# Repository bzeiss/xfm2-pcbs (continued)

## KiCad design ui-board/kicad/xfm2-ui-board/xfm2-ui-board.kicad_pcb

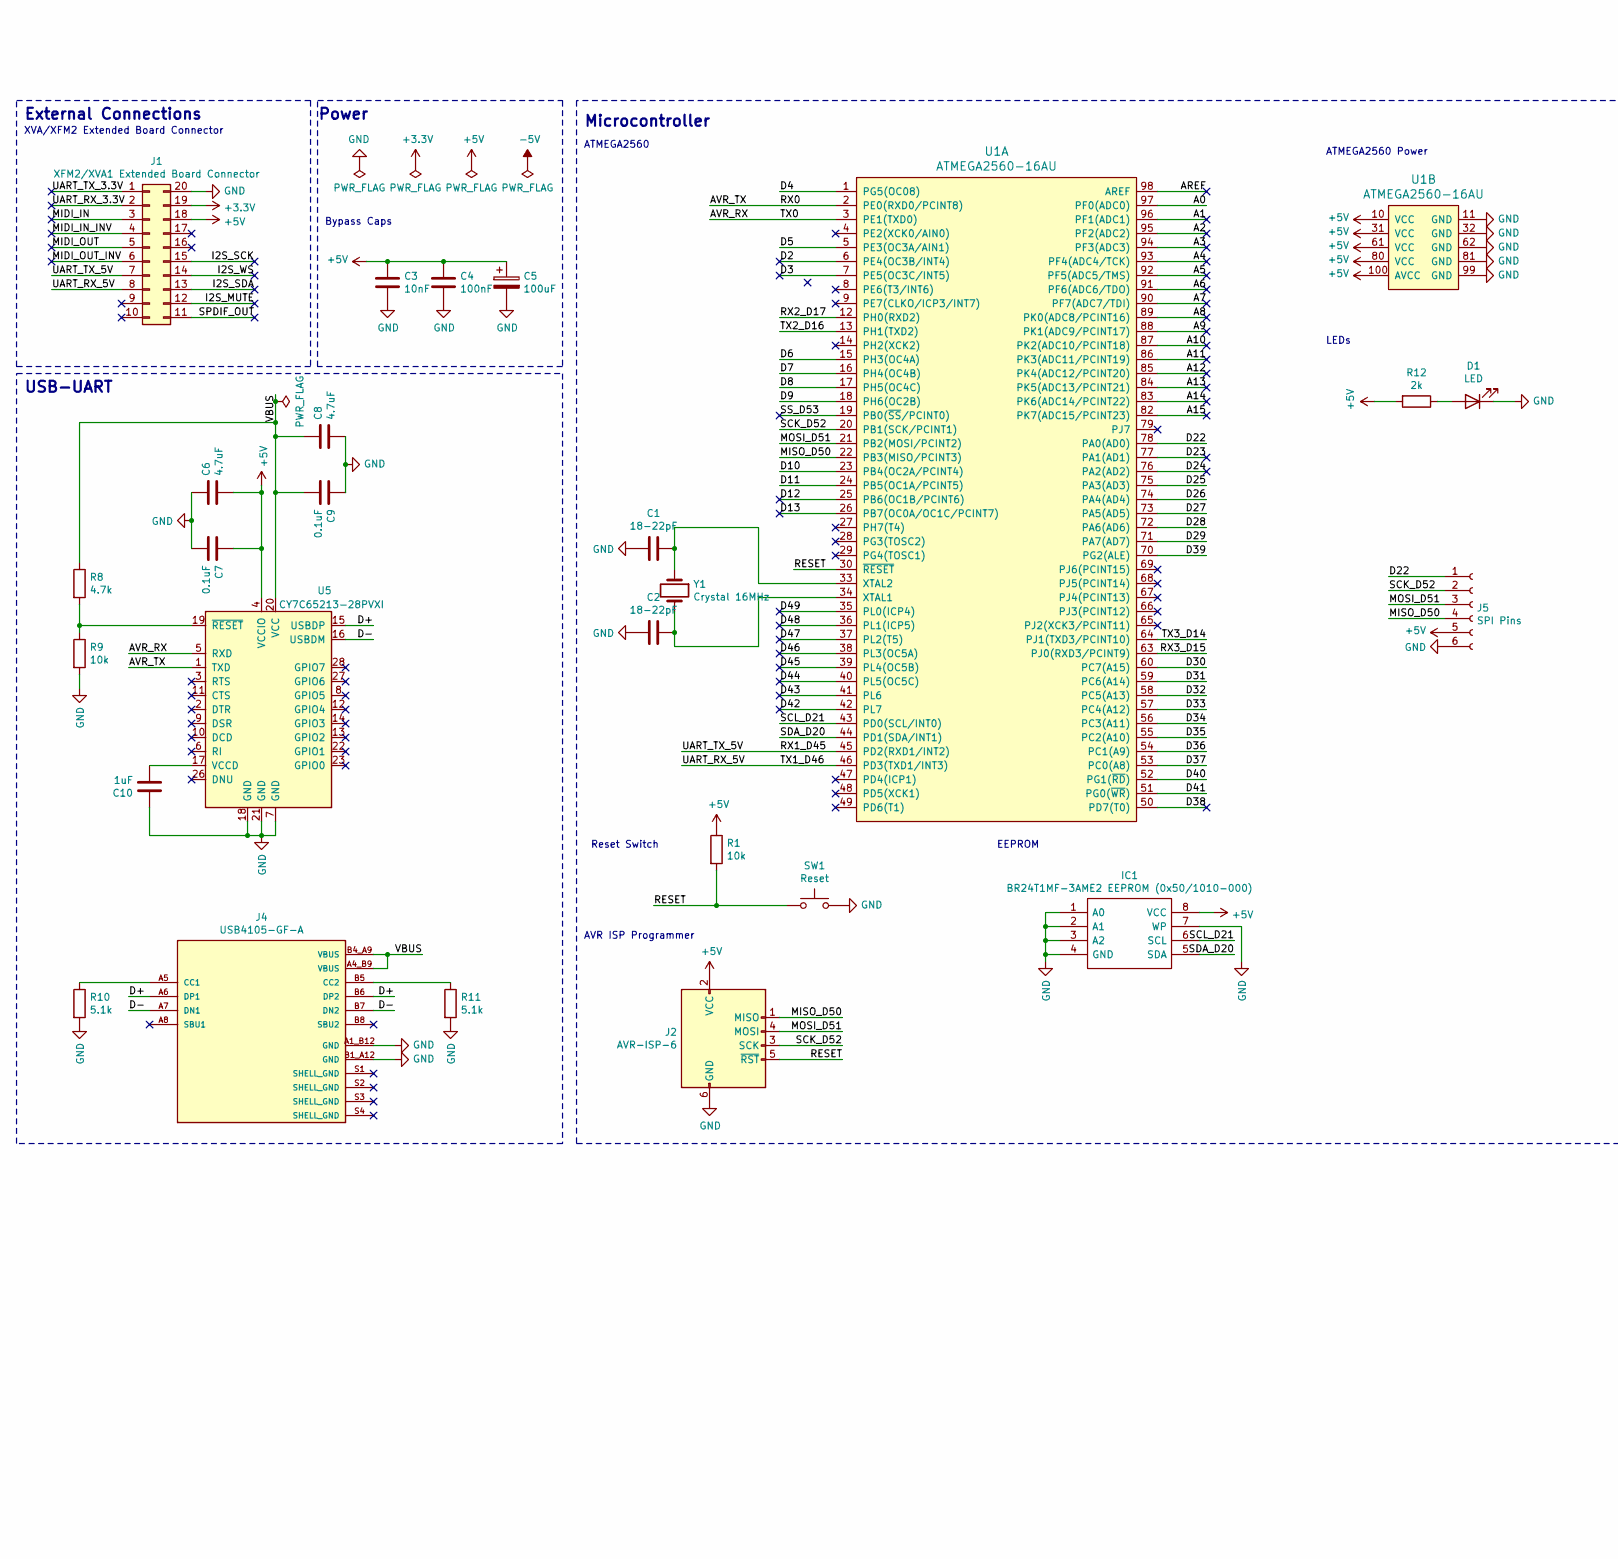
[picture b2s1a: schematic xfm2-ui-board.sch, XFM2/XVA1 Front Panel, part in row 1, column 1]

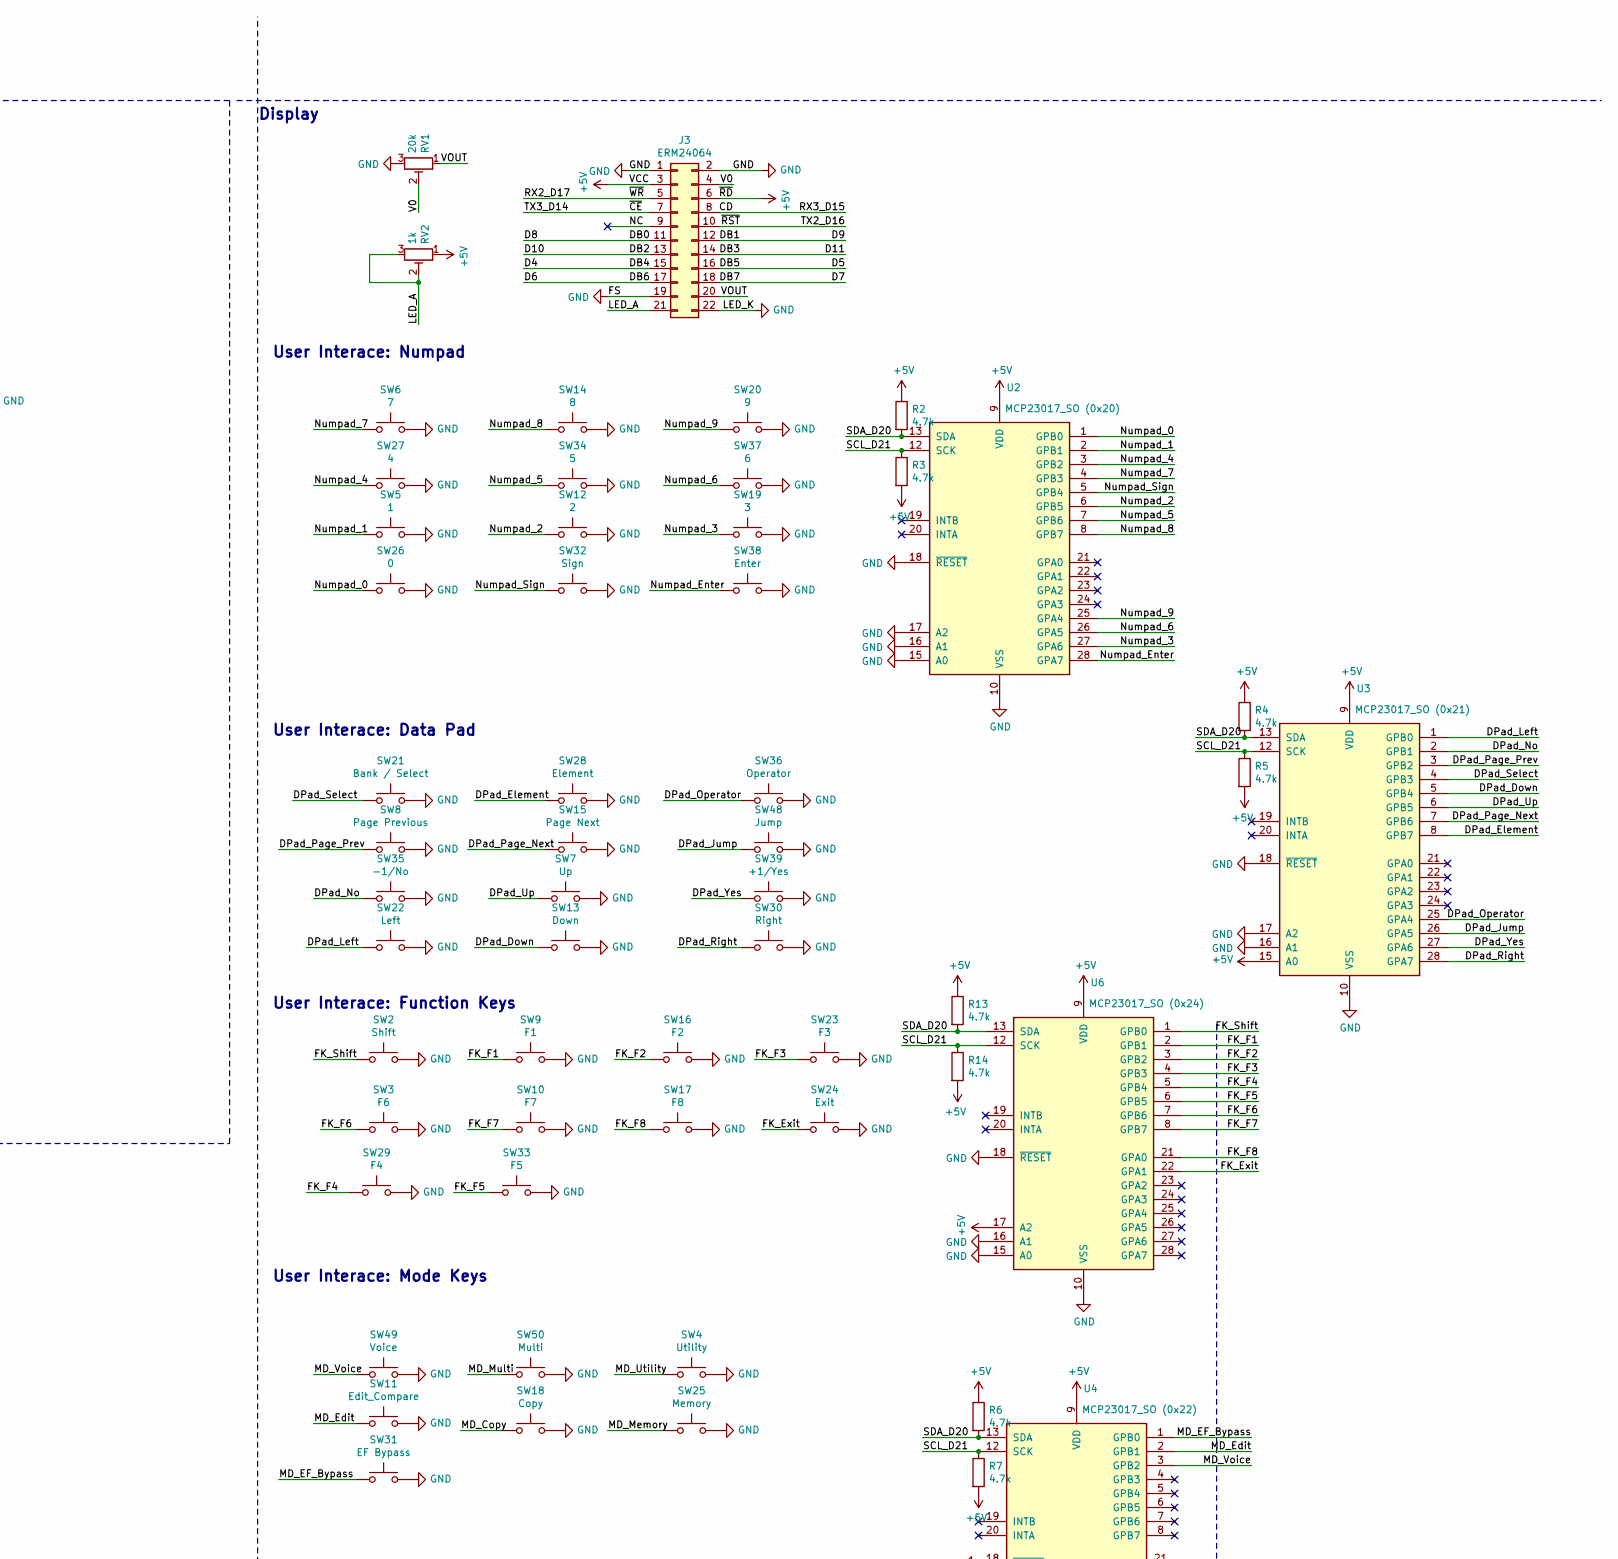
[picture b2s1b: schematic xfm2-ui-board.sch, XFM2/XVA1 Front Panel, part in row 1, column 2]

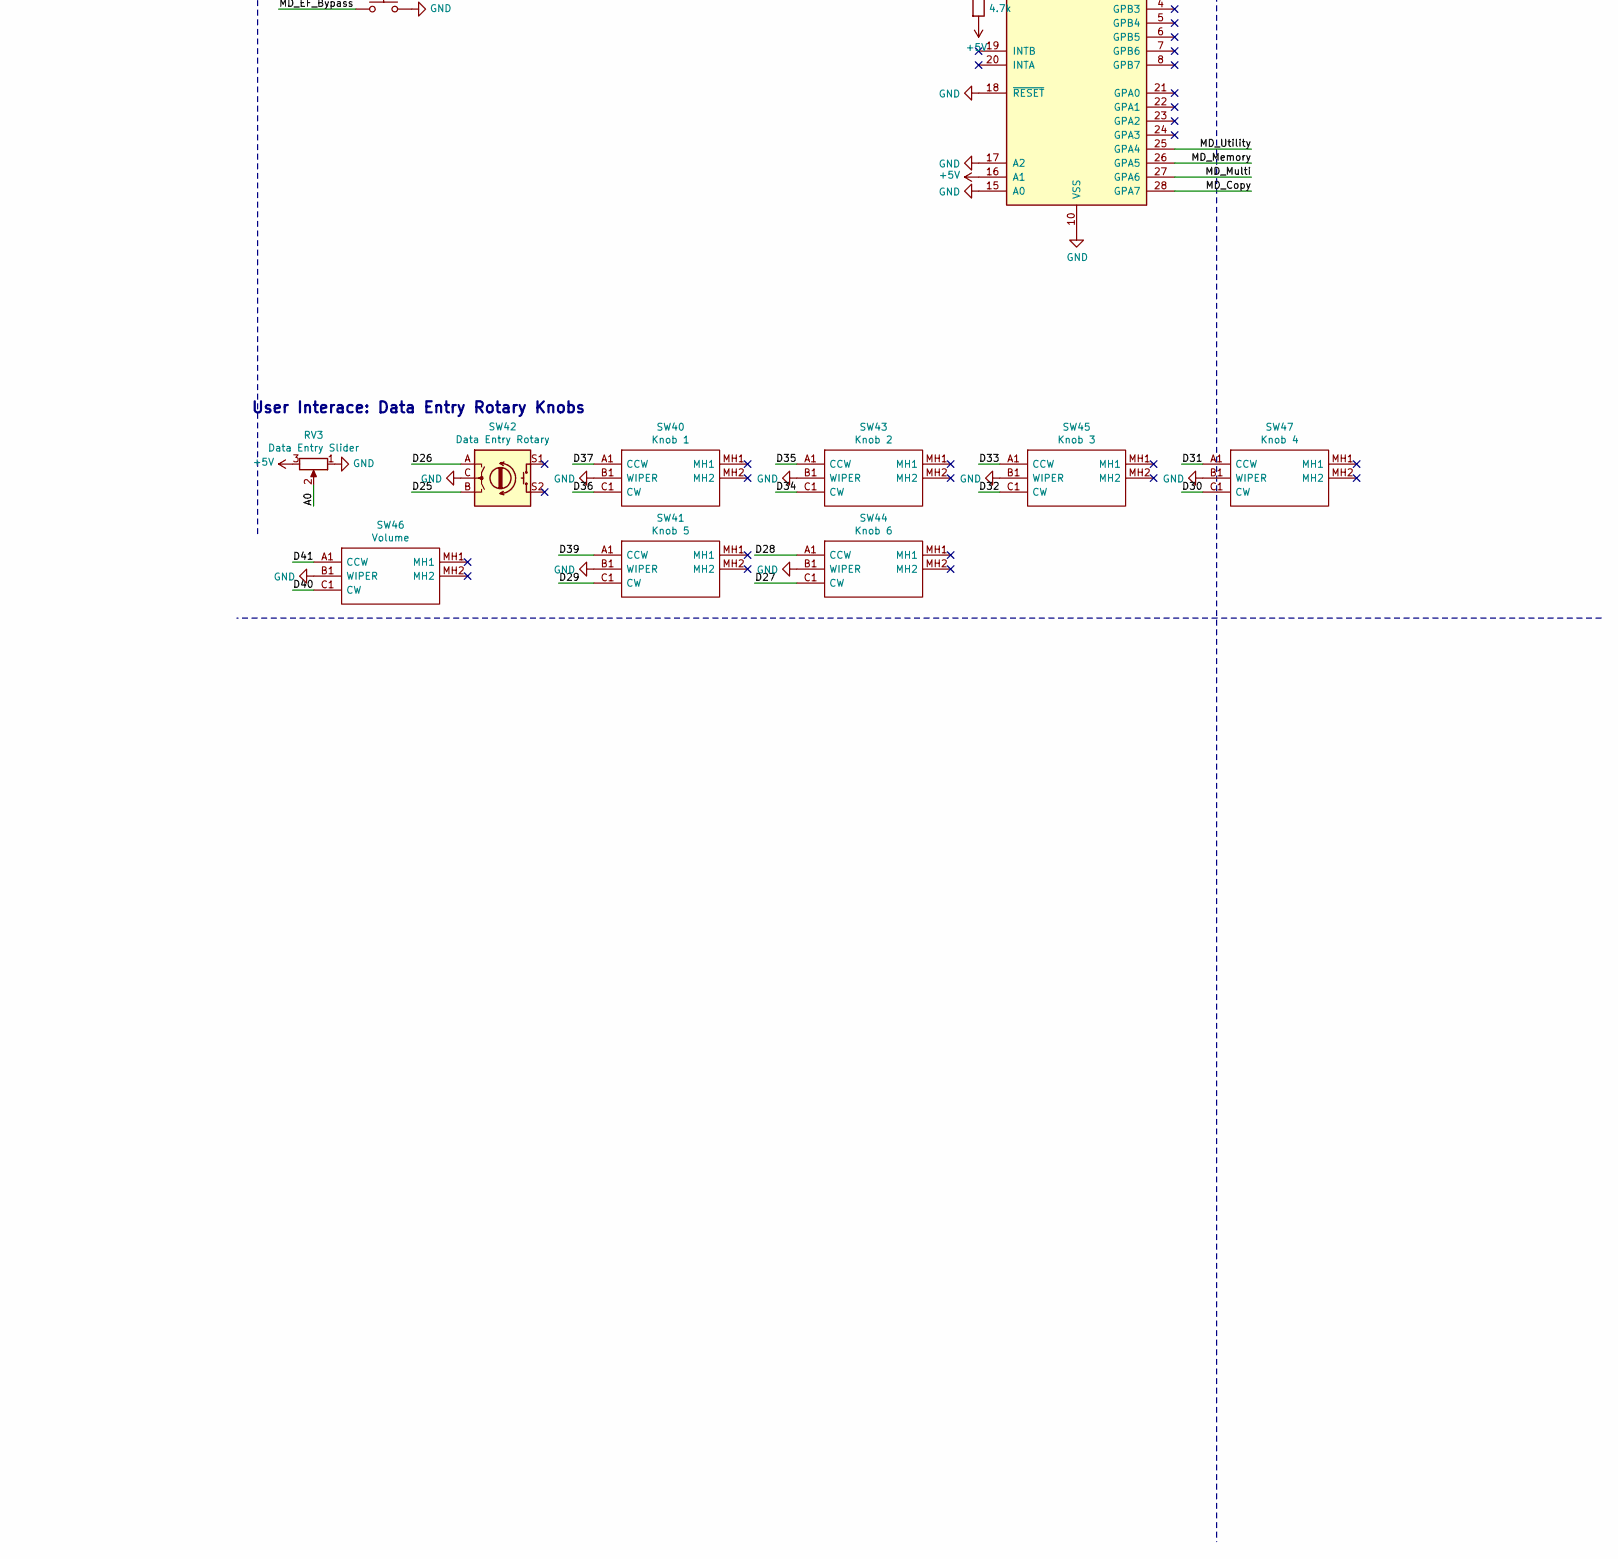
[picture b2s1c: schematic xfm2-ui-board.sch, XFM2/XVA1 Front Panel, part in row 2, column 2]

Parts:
C1, C2: 18-22pF; C_0805_2012Metric_Pad1.18x1.45mm_HandSolder
C3: 10nF; C_0805_2012Metric_Pad1.18x1.45mm_HandSolder
C4: 100nF; C_0805_2012Metric_Pad1.18x1.45mm_HandSolder
C5: 100uF; CP_Elec_5x4.4
C6, C8: 4.7uF; C_0805_2012Metric_Pad1.18x1.45mm_HandSolder
C7, C9: 0.1uF; C_0805_2012Metric_Pad1.18x1.45mm_HandSolder
C10: 1uF; C_0805_2012Metric_Pad1.18x1.45mm_HandSolder
D1: LED; LED_0805_2012Metric_Pad1.15x1.40mm_HandSolder
IC1: BR24T1MF-3AME2 EEPROM (0x50/1010-000); SOIC127P620X171-8N; Mouser Part Number 755-BR24T1MF-3AME2
J1: XFM2/XVA1 Extended Board Connector; PinHeader_2x10_P2.54mm_Vertical
J2: AVR-ISP-6; PinHeader_1x06_P2.54mm_Vertical
J3: ERM24064; PinHeader_2x11_P2.54mm_Vertical
J4: USB4105-GF-A; GCT_USB4105-GF-A; PARTREV A3
J5: SPI Pins; PinHeader_1x06_P2.54mm_Vertical
R1, R9: 10k; R_0805_2012Metric_Pad1.20x1.40mm_HandSolder
R2, R3, R4, R5, R6, R7, R8, R13, R14: 4.7k; R_0805_2012Metric_Pad1.20x1.40mm_HandSolder
R10, R11: 5.1k; R_0805_2012Metric_Pad1.20x1.40mm_HandSolder
R12: 2k; R_0805_2012Metric_Pad1.20x1.40mm_HandSolder
RV1: 20k; Potentiometer_ACP_CA9-V10_Vertical
RV2: 1k; Potentiometer_ACP_CA9-V10_Vertical
RV3: Data Entry Slider; RS30111A9012
SW1: Reset; SW_PUSH_6mm
SW2: Shift; SW_PUSH_6mm
SW3: F6; SW_PUSH_6mm
SW4: Utility; SW_PUSH_6mm
SW5: 1; SW_PUSH_6mm
SW6: 7; SW_PUSH_6mm
SW7: Up; SW_PUSH_6mm
SW8: Page Previous; SW_PUSH_6mm
SW9: F1; SW_PUSH_6mm
SW10: F7; SW_PUSH_6mm
SW11: Edit_Compare; SW_PUSH_6mm
SW12: 2; SW_PUSH_6mm
SW13: Down; SW_PUSH_6mm
SW14: 8; SW_PUSH_6mm
SW15: Page Next; SW_PUSH_6mm
SW16: F2; SW_PUSH_6mm
SW17: F8; SW_PUSH_6mm
SW18: Copy; SW_PUSH_6mm
SW19: 3; SW_PUSH_6mm
SW20: 9; SW_PUSH_6mm
SW21: Bank / Select; SW_PUSH_6mm
SW22: Left; SW_PUSH_6mm
SW23: F3; SW_PUSH_6mm
SW24: Exit; SW_PUSH_6mm
SW25: Memory; SW_PUSH_6mm
SW26: 0; SW_PUSH_6mm
SW27: 4; SW_PUSH_6mm
SW28: Element; SW_PUSH_6mm
SW29: F4; SW_PUSH_6mm
SW30: Right; SW_PUSH_6mm
SW31: EF Bypass; SW_PUSH_6mm
SW32: Sign; SW_PUSH_6mm
SW33: F5; SW_PUSH_6mm
SW34: 5; SW_PUSH_6mm
SW35: -1/No; SW_PUSH_6mm
SW36: Operator; SW_PUSH_6mm
SW37: 6; SW_PUSH_6mm
SW38: Enter; SW_PUSH_6mm
SW39: +1/Yes; SW_PUSH_6mm
SW40: Knob 1; PEC164015FN0024; Mouser Part Number 652-PEC16-4015FN0024
SW41: Knob 5; PEC164015FN0024; Mouser Part Number 652-PEC16-4015FN0024
SW42: Data Entry Rotary; RotaryEncoder_Alps_EC11E-Switch_Vertical_H20mm
SW43: Knob 2; PEC164015FN0024; Mouser Part Number 652-PEC16-4015FN0024
SW44: Knob 6; PEC164015FN0024; Mouser Part Number 652-PEC16-4015FN0024
SW45: Knob 3; PEC164015FN0024; Mouser Part Number 652-PEC16-4015FN0024
SW46: Volume; PEC164015FN0024; Mouser Part Number 652-PEC16-4015FN0024
SW47: Knob 4; PEC164015FN0024; Mouser Part Number 652-PEC16-4015FN0024
SW48: Jump; SW_PUSH_6mm
SW49: Voice; SW_PUSH_6mm
SW50: Multi; SW_PUSH_6mm
U1: ATMEGA2560-16AU; TQFP-100_14x14mm; MPN ATMEGA2560-16AU; Digi-Key_PN ATMEGA2560-16AU-ND
U2: MCP23017_SO (0x20); SOIC-28W_7.5x17.9mm_P1.27mm
U3: MCP23017_SO (0x21); SOIC-28W_7.5x17.9mm_P1.27mm
U4: MCP23017_SO (0x22); SOIC-28W_7.5x17.9mm_P1.27mm
U5: CY7C65213-28PVXI; SSOP-28_5.3x10.2mm_P0.65mm
U6: MCP23017_SO (0x24); SOIC-28W_7.5x17.9mm_P1.27mm
Y1: Crystal 16MHz; Crystal_SMD_3225-4Pin_3.2x2.5mm_HandSoldering

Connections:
+3V3: J1.19
+5V: C3.2, C4.2, C5.1, C6.2, C7.1, IC1.8 (VCC), J1.18, J2.2 (VCC), J3.3, J3.6, J5.5, R1.1, R2.1, R3.2, R4.1, R5.2, R6.1, R7.2, R12.2, R13.1, R14.2, RV2.1, RV3.3, U1.10 (VCC), U1.31 (VCC), U1.61 (VCC), U1.80 (VCC), U1.100 (AVCC), U2.9 (VDD), U3.9 (VDD), U3.15 (A0), U4.9 (VDD), U4.16 (A1), U5.4 (VCCIO), U6.9 (VDD), U6.17 (A2)
/A0: RV3.2, U1.97 (PF0(ADC0))
/A1: U1.96 (PF1(ADC1))
/A2: U1.95 (PF2(ADC2))
/A3: U1.94 (PF3(ADC3))
/A4: U1.93 (PF4(ADC4/TCK))
/A5: U1.92 (PF5(ADC5/TMS))
/A6: U1.91 (PF6(ADC6/TDO))
/A7: U1.90 (PF7(ADC7/TDI))
/A8: U1.89 (PK0(ADC8/PCINT16))
/A9: U1.88 (PK1(ADC9/PCINT17))
/A10: U1.87 (PK2(ADC10/PCINT18))
/A11: U1.86 (PK3(ADC11/PCINT19))
/A12: U1.85 (PK4(ADC12/PCINT20))
/A13: U1.84 (PK5(ADC13/PCINT21))
/A14: U1.83 (PK6(ADC14/PCINT22))
/A15: U1.82 (PK7(ADC15/PCINT23))
/AREF: U1.98 (AREF)
/AVR_RX: U1.3 (PE1(TXD0)), U5.5 (RXD)
/AVR_TX: U1.2 (PE0(RXD0/PCINT8)), U5.1 (TXD)
/CD: J3.8, U1.63 (PJ0(RXD3/PCINT9))
/D2: U1.6 (PE4(OC3B/INT4))
/D3: U1.7 (PE5(OC3C/INT5))
/D4: J3.15, U1.1 (PG5(OC08))
/D5: J3.16, U1.5 (PE3(OC3A/AIN1))
/D6: J3.17, U1.15 (PH3(OC4A))
/D7: J3.18, U1.16 (PH4(OC4B))
/D8: J3.11, U1.17 (PH5(OC4C))
/D9: J3.12, U1.18 (PH6(OC2B))
/D10: J3.13, U1.23 (PB4(OC2A/PCINT4))
/D11: J3.14, U1.24 (PB5(OC1A/PCINT5))
/D12: U1.25 (PB6(OC1B/PCINT6))
/D13: U1.26 (PB7(OC0A/OC1C/PCINT7))
/D22: J5.1, U1.78 (PA0(AD0))
/D23: U1.77 (PA1(AD1))
/D24: U1.76 (PA2(AD2))
/D25: SW42.B, U1.75 (PA3(AD3))
/D26: SW42.A, U1.74 (PA4(AD4))
/D27: SW44.C1 (CW), U1.73 (PA5(AD5))
/D28: SW44.A1 (CCW), U1.72 (PA6(AD6))
/D29: SW41.C1 (CW), U1.71 (PA7(AD7))
/D30: SW47.C1 (CW), U1.60 (PC7(A15))
/D31: SW47.A1 (CCW), U1.59 (PC6(A14))
/D32: SW45.C1 (CW), U1.58 (PC5(A13))
/D33: SW45.A1 (CCW), U1.57 (PC4(A12))
/D34: SW43.C1 (CW), U1.56 (PC3(A11))
/D35: SW43.A1 (CCW), U1.55 (PC2(A10))
/D36: SW40.C1 (CW), U1.54 (PC1(A9))
/D37: SW40.A1 (CCW), U1.53 (PC0(A8))
/D38: U1.50 (PD7(T0))
/D39: SW41.A1 (CCW), U1.70 (PG2(ALE))
/D40: SW46.C1 (CW), U1.52 (PG1(~RD~))
/D41: SW46.A1 (CCW), U1.51 (PG0(~WR~))
/D42: U1.42 (PL7)
/D43: U1.41 (PL6)
/D44: U1.40 (PL5(OC5C))
/D45: U1.39 (PL4(OC5B))
/D46: U1.38 (PL3(OC5A))
/D47: U1.37 (PL2(T5))
/D48: U1.36 (PL1(ICP5))
/D49: U1.35 (PL0(ICP4))
/D+: J4.A6 (DP1), J4.B6 (DP2), U5.15 (USBDP)
/D-: J4.A7 (DN1), J4.B7 (DN2), U5.16 (USBDM)
/DPad_Down: SW13.1, U3.5 (GPB4)
/DPad_Element: SW28.1, U3.8 (GPB7)
/DPad_Jump: SW48.1, U3.26 (GPA5)
/DPad_Left: SW22.1, U3.1 (GPB0)
/DPad_No: SW35.1, U3.2 (GPB1)
/DPad_Operator: SW36.1, U3.25 (GPA4)
/DPad_Page_Next: SW15.1, U3.7 (GPB6)
/DPad_Page_Prev: SW8.1, U3.3 (GPB2)
/DPad_Right: SW30.1, U3.28 (GPA7)
/DPad_Select: SW21.1, U3.4 (GPB3)
/DPad_Up: SW7.1, U3.6 (GPB5)
/DPad_Yes: SW39.1, U3.27 (GPA6)
/FK_Exit: SW24.1, U6.22 (GPA1)
/FK_F1: SW9.1, U6.2 (GPB1)
/FK_F2: SW16.1, U6.3 (GPB2)
/FK_F3: SW23.1, U6.4 (GPB3)
/FK_F4: SW29.1, U6.5 (GPB4)
/FK_F5: SW33.1, U6.6 (GPB5)
/FK_F6: SW3.1, U6.7 (GPB6)
/FK_F7: SW10.1, U6.8 (GPB7)
/FK_F8: SW17.1, U6.21 (GPA0)
/FK_Shift: SW2.1, U6.1 (GPB0)
/I2S_MUTE: J1.12
/I2S_SCK: J1.15
/I2S_SDA: J1.13
/I2S_WS: J1.14
/LED_A: J3.21, RV2.2, RV2.3
/MD_Copy: SW18.1, U4.28 (GPA7)
/MD_EF_Bypass: SW31.1, U4.1 (GPB0)
/MD_Edit: SW11.1, U4.2 (GPB1)
/MD_Memory: SW25.1, U4.26 (GPA5)
/MD_Multi: SW50.1, U4.27 (GPA6)
/MD_Utility: SW4.1, U4.25 (GPA4)
/MD_Voice: SW49.1, U4.3 (GPB2)
/MIDI_IN: J1.3
/MIDI_IN_INV: J1.4
/MIDI_OUT: J1.5
/MIDI_OUT_INV: J1.6
/MISO_D50: J2.1 (MISO), J5.4, U1.22 (PB3(MISO/PCINT3))
/MOSI_D51: J2.4 (MOSI), J5.3, U1.21 (PB2(MOSI/PCINT2))
/NC: J3.9
/Numpad_0: SW26.1, U2.1 (GPB0)
/Numpad_1: SW5.1, U2.2 (GPB1)
/Numpad_2: SW12.1, U2.6 (GPB5)
/Numpad_3: SW19.1, U2.27 (GPA6)
/Numpad_4: SW27.1, U2.3 (GPB2)
/Numpad_5: SW34.1, U2.7 (GPB6)
/Numpad_6: SW37.1, U2.26 (GPA5)
/Numpad_7: SW6.1, U2.4 (GPB3)
/Numpad_8: SW14.1, U2.8 (GPB7)
/Numpad_9: SW20.1, U2.25 (GPA4)
/Numpad_Enter: SW38.1, U2.28 (GPA7)
/Numpad_Sign: SW32.1, U2.5 (GPB4)
/RESET: J2.5 (~RST), R1.2, SW1.1, U1.30 (~RESET)
/RX1_D45: J1.7, U1.45 (PD2(RXD1/INT2))
/RX2_D17: J3.5, U1.12 (PH0(RXD2))
/SCK_D52: J2.3 (SCK), J5.2, U1.20 (PB1(SCK/PCINT1))
/SCL_D21: IC1.6 (SCL), R3.1, R5.1, R7.1, R14.1, U1.43 (PD0(SCL/INT0)), U2.12 (SCK), U3.12 (SCK), U4.12 (SCK), U6.12 (SCK)
/SDA_D20: IC1.5 (SDA), R2.2, R4.2, R6.2, R13.2, U1.44 (PD1(SDA/INT1)), U2.13 (SDA), U3.13 (SDA), U4.13 (SDA), U6.13 (SDA)
/SPDIF_OUT: J1.11
/SS_D53: U1.19 (PB0(~SS~/PCINT0))
/TX1_D46: J1.8, U1.46 (PD3(TXD1/INT3))
/TX2_D16: J3.10, U1.13 (PH1(TXD2))
/TX3_D14: J3.7, U1.64 (PJ1(TXD3/PCINT10))
/UART_RX_3.3V: J1.2
/UART_TX_3.3V: J1.1
/V0: J3.4, RV1.2
/VBUS: C8.1, C9.2, J4.A4_B9 (VBUS), J4.B4_A9 (VBUS), R8.1, U5.20 (VCC)
/VOUT: J3.20, RV1.1
GND: C1.2, C2.2, C3.1, C4.1, C5.2, C6.1, C7.2, C8.2, C9.1, C10.1, D1.1 (K), IC1.1 (A0), IC1.2 (A1), IC1.3 (A2), IC1.4 (GND), IC1.7 (WP), J1.20, J2.6 (GND), J3.1, J3.2, J3.19, J3.22, J4.A1_B12 (GND), J4.B1_A12 (GND), J5.6, R9.2, R10.2, R11.2, RV1.3, RV3.1, SW1.2, SW2.2, SW3.2, SW4.2, SW5.2, SW6.2, SW7.2, SW8.2, SW9.2, SW10.2, SW11.2, SW12.2, SW13.2, SW14.2, SW15.2, SW16.2, SW17.2, SW18.2, SW19.2, SW20.2, SW21.2, SW22.2, SW23.2, SW24.2, SW25.2, SW26.2, SW27.2, SW28.2, SW29.2, SW30.2, SW31.2, SW32.2, SW33.2, SW34.2, SW35.2, SW36.2, SW37.2, SW38.2, SW39.2, SW40.B1 (WIPER), SW41.B1 (WIPER), SW42.C, SW43.B1 (WIPER), SW44.B1 (WIPER), SW45.B1 (WIPER), SW46.B1 (WIPER), SW47.B1 (WIPER), SW48.2, SW49.2, SW50.2, U1.11 (GND), U1.32 (GND), U1.62 (GND), U1.81 (GND), U1.99 (GND), U2.10 (VSS), U2.15 (A0), U2.16 (A1), U2.17 (A2), U2.18 (~RESET~), U3.10 (VSS), U3.16 (A1), U3.17 (A2), U3.18 (~RESET~), U4.10 (VSS), U4.15 (A0), U4.17 (A2), U4.18 (~RESET~), U5.7 (GND), U5.18 (GND), U5.21 (GND), U6.10 (VSS), U6.15 (A0), U6.16 (A1), U6.18 (~RESET~)
unnamed: C1.1, U1.33 (XTAL2), Y1.1
unnamed: C2.1, U1.34 (XTAL1), Y1.2
unnamed: C10.2, U5.17 (VCCD)
unnamed: D1.2 (A), R12.1
unnamed: J4.A5 (CC1), R10.1
unnamed: J4.B5 (CC2), R11.1
unnamed: R8.2, R9.1, U5.19 (~RESET)

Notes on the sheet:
External Connections
XVA/XFM2 Extended Board Connector
AVR ISP Programmer
Microcontroller
ATMEGA2560
Reset Switch
Display
Bypass Caps
User Interace: Data Entry Rotary Knobs
ATMEGA2560 Power
Power
USB-UART
EEPROM
LEDs
User Interace: Mode Keys
User Interace: Function Keys
User Interace: Data Pad
User Interace: Numpad

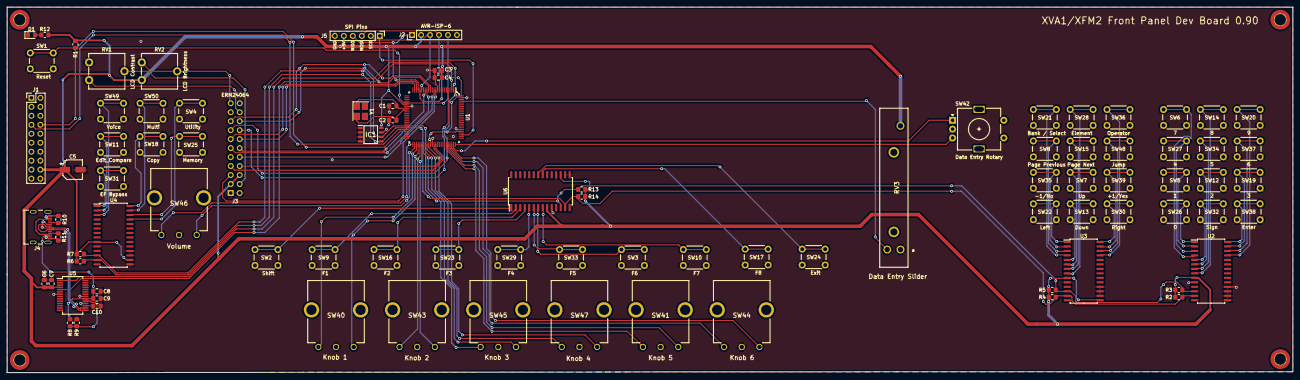
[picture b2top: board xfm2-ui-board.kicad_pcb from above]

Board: 2 copper layers, 363.7 x 103.4 mm, 91 parts (1 on the bottom side), 96 nets.

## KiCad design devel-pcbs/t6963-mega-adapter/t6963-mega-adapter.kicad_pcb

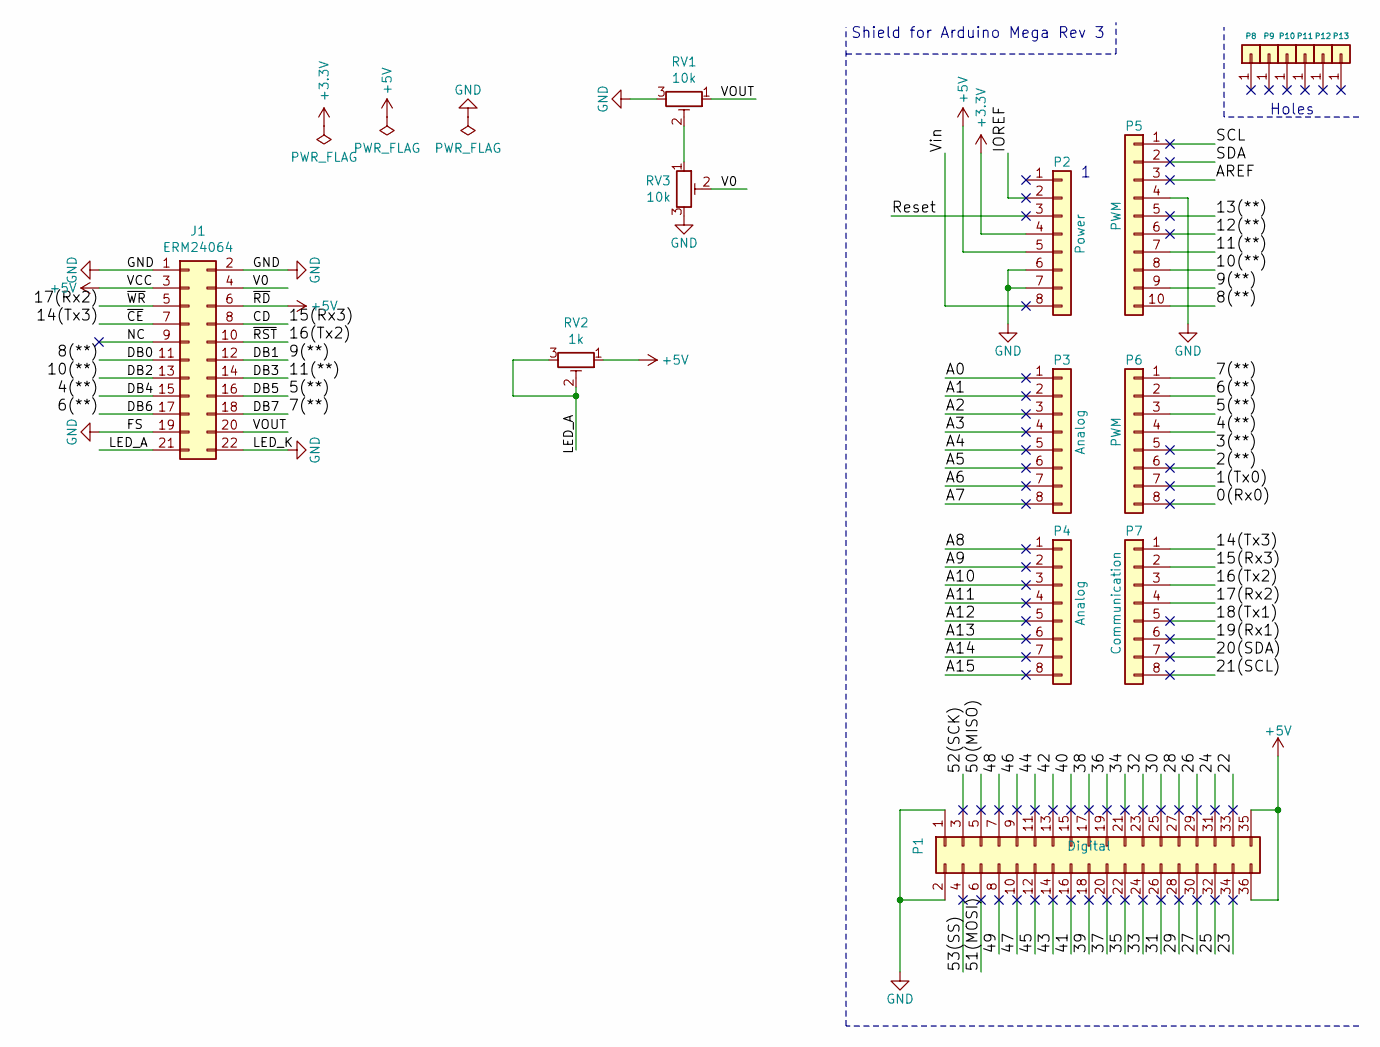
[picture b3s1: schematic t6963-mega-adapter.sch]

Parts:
J1: ERM24064; PinHeader_2x11_P2.54mm_Vertical
P1: Digital; Socket_Strip_Arduino_2x18
P2: Power; Socket_Strip_Arduino_1x08
P3, P4: Analog; Socket_Strip_Arduino_1x08
P5: PWM; Socket_Strip_Arduino_1x10
P6: PWM; Socket_Strip_Arduino_1x08
P7: Communication; Socket_Strip_Arduino_1x08
P8, P9, P10, P11, P12, P13: CONN_01X01; Arduino_1pin
RV1, RV3: 10k; Potentiometer_ACP_CA9-V10_Vertical
RV2: 1k; Potentiometer_ACP_CA9-V10_Vertical

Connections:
+3V3: P2.4
+5V: J1.3, J1.6, P1.35, P1.36, P2.5, RV2.1
/0(Rx0): P6.8
/1(Tx0): P6.7
/2(**): P6.6
/3(**): P6.5
/4(**): J1.15, P6.4
/5(**): J1.16, P6.3
/6(**): J1.17, P6.2
/7(**): J1.18, P6.1
/8(**): J1.11, P5.10
/9(**): J1.12, P5.9
/10(**): J1.13, P5.8
/11(**): J1.14, P5.7
/12(**): P5.6
/13(**): P5.5
/14(Tx3): J1.7, P7.1
/15(Rx3): J1.8, P7.2
/16(Tx2): J1.10, P7.3
/17(Rx2): J1.5, P7.4
/18(Tx1): P7.5
/19(Rx1): P7.6
/20(SDA): P7.7
/21(SCL): P7.8
/22: P1.33
/23: P1.34
/24: P1.31
/25: P1.32
/26: P1.29
/27: P1.30
/28: P1.27
/29: P1.28
/30: P1.25
/31: P1.26
/32: P1.23
/33: P1.24
/34: P1.21
/35: P1.22
/36: P1.19
/37: P1.20
/38: P1.17
/39: P1.18
/40: P1.15
/41: P1.16
/42: P1.13
/43: P1.14
/44: P1.11
/45: P1.12
/46: P1.9
/47: P1.10
/48: P1.7
/49: P1.8
/50(MISO): P1.5
/51(MOSI): P1.6
/52(SCK): P1.3
/53(SS): P1.4
/A0: P3.1
/A1: P3.2
/A2: P3.3
/A3: P3.4
/A4: P3.5
/A5: P3.6
/A6: P3.7
/A7: P3.8
/A8: P4.1
/A9: P4.2
/A10: P4.3
/A11: P4.4
/A12: P4.5
/A13: P4.6
/A14: P4.7
/A15: P4.8
/AREF: P5.3
/IOREF: P2.2
/LED_A: J1.21, RV2.2, RV2.3
/NC: J1.9
/Reset: P2.3
/SCL: P5.1
/SDA: P5.2
/V0: J1.4, RV3.2
/VOUT: J1.20, RV1.1
/Vin: P2.8
GND: J1.1, J1.2, J1.19, J1.22, P1.1, P1.2, P2.6, P2.7, P5.4, RV1.3, RV3.3
unnamed: RV1.2, RV3.1

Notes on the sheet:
Shield for Arduino Mega Rev 3
Holes

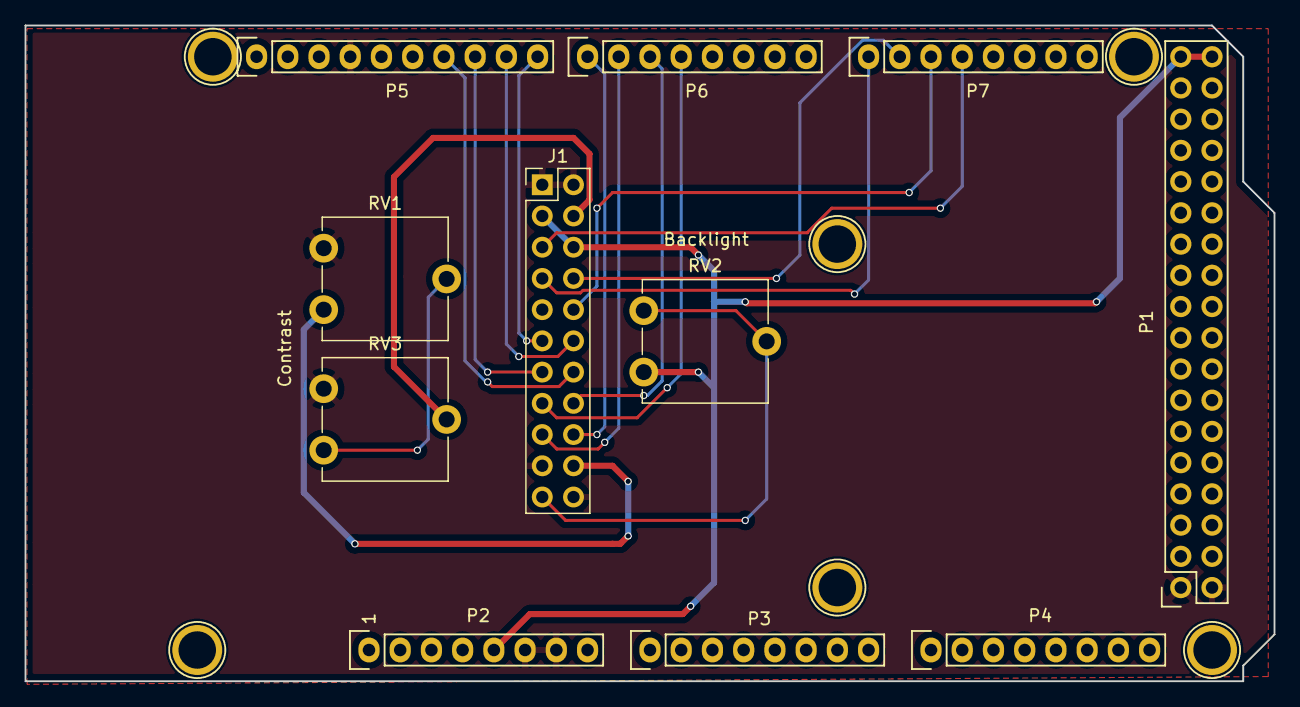
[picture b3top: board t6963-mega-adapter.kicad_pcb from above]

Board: 2 copper layers, 101.6 x 53.3 mm, 17 parts (0 on the bottom side), 18 nets.

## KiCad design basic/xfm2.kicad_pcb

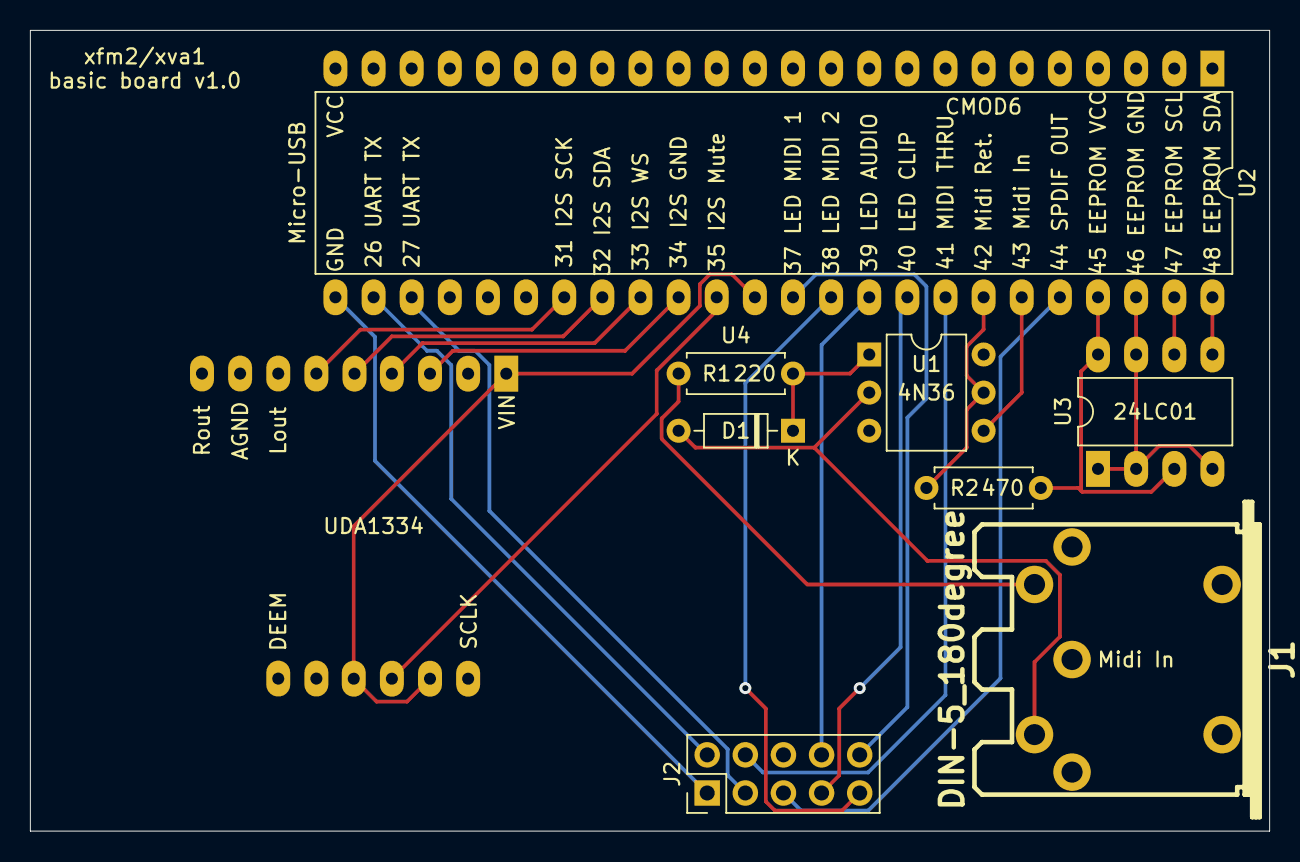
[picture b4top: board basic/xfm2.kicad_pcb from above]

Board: 2 copper layers, 82.6 x 53.3 mm, 9 parts (0 on the bottom side), 24 nets.

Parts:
D1: D; D_DO-35_SOD27_P7.62mm_Horizontal
J1: DIN-5_180degree; din-5
J2: Conn_02x05_Counter_Clockwise; PinHeader_2x05_P2.54mm_Vertical
R1: 220; R_Axial_DIN0207_L6.3mm_D2.5mm_P7.62mm_Horizontal
R2: 470; R_Axial_DIN0207_L6.3mm_D2.5mm_P7.62mm_Horizontal
U1: 4N36; DIP-6_W7.62mm
U2: CmodA7-35T; DIP-48_W15.24mm_LongPads
U3: 24LC01; DIP-8_W7.62mm_LongPads
U4: UDA1334A; Adafruit_UDA1334A_Breakout

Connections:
/*UART_RX: J2.3, U2.27
/*UART_TX: J2.2, U2.26
/EEPROM_GND: U2.46, U3.1, U3.2, U3.4, U3.7
/EEPROM_SCL: U2.47, U3.6
/EEPROM_SDA: U2.48, U3.5
/EEPROM_VCC: R2.1, U2.45, U3.3, U3.8
/I2S_GND: U2.34, U4.3
/I2S_MUTE: U2.35, U4.12
/I2S_SCK: U2.31, U4.6
/I2S_SDA: U2.32, U4.5
/I2S_VCC: U2.36, U4.1, U4.11, U4.13
/I2S_WS: U2.33, U4.4
/MIDI_IN: U1.4, U2.43
/MIDI_RETURN: R2.2, U1.5, U2.42
/MIDI_TX: D1.1, R1.2, U1.1
/MIDI_TX_RETURN: D1.2, J1.5, U1.2
GND: J2.1, U2.25
LED_AUDIO: J2.8, U2.39
LED_CLIP: J2.7, U2.40
LED_MIDI_1: J2.10, U2.37
LED_MIDI_2: J2.9, U2.38
MIDI_THRU: J2.4, U2.41
unnamed: J1.4, R1.1
SPDIF_OUT: J2.5, U2.44

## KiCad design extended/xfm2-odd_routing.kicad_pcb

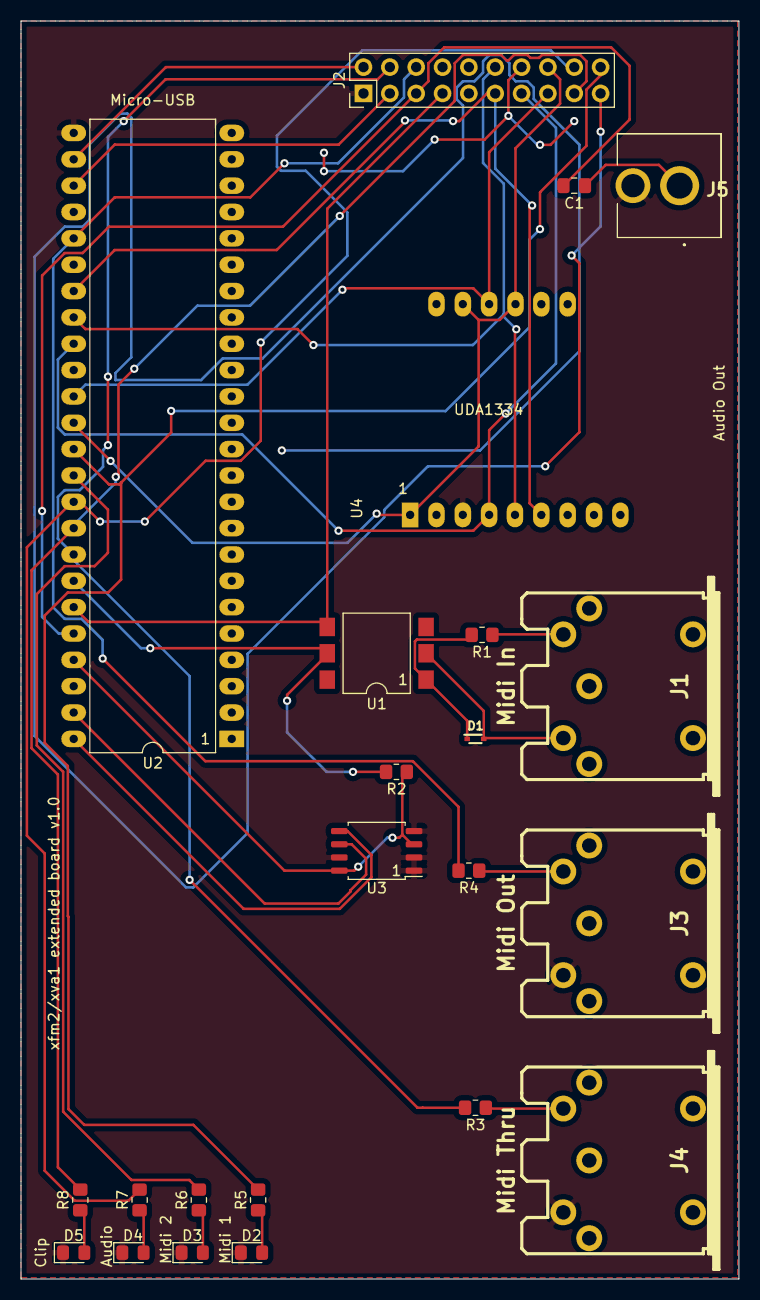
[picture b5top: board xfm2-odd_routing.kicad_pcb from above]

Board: 2 copper layers, 69.2 x 121.3 mm, 23 parts (0 on the bottom side), 30 nets.

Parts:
C1: 10nF; C_0805_2012Metric_Pad1.18x1.45mm_HandSolder
D1: D; SODFL1608X70N
D2: LED_MIDI_1; LED_0805_2012Metric_Pad1.15x1.40mm_HandSolder
D3: LED_MIDI_2; LED_0805_2012Metric_Pad1.15x1.40mm_HandSolder
D4: LED_AUDIO; LED_0805_2012Metric_Pad1.15x1.40mm_HandSolder
D5: LED_CLIP; LED_0805_2012Metric_Pad1.15x1.40mm_HandSolder
J1: Midi In; din-5
J2: Pin Breakout; PinHeader_2x10_P2.54mm_Vertical
J3: Midi Out; din-5
J4: Midi Thru; din-5
J5: Conn_Coaxial; KLPX0848A2Y
R1, R5, R6, R7, R8: 220; R_0805_2012Metric_Pad1.20x1.40mm_HandSolder
R2: 470; R_0805_2012Metric_Pad1.20x1.40mm_HandSolder
R3, R4: 33; R_0805_2012Metric_Pad1.20x1.40mm_HandSolder
U1: 4N36; SMDIP-6_W9.53mm_Clearance8mm
U2: CmodA7-35T; DIP-48_W15.24mm_LongPads
U3: 24LC01; SOIC-8_5.275x5.275mm_P1.27mm
U4: UDA1334A; Adafruit_UDA1334A_Breakout

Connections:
/*UART_RX: J2.3, U2.27
/*UART_TX: J2.2, U2.26
/EEPROM_SCL: U2.47, U3.6
/EEPROM_SDA: U2.48, U3.5
/EEPROM_VCC: R2.1, U2.45, U3.3, U3.8
/MIDI_TX: D1.1, R1.2, U1.1
/MIDI_TX_RETURN: D1.2, J1.5, U1.2
GND: D2.1, D3.1, D4.1, D5.1, J2.1, J2.14, J3.5, J4.5, J5.2, U2.25, U3.1, U3.2, U3.4, U3.7, U4.3
I2S_MUTE: J2.15, U2.35, U4.12
I2S_SCK: J2.11, U2.31, U4.6
I2S_SDA: J2.12, U2.32, U4.5
I2S_VCC: J2.16, U2.36, U4.1, U4.11, U4.13
I2S_WS: J2.13, U2.33, U4.4
LED_AUDIO: J2.18, R7.2, U2.39
LED_CLIP: J2.17, R8.2, U2.40
LED_MIDI_1: J2.20, R5.2, U2.37
LED_MIDI_2: J2.19, R6.2, U2.38
MIDI_IN: J2.7, U1.4, U2.43
MIDI_IN_RETURN: R2.2, U1.5, U2.42
MIDI_OUT: J2.6, R4.2, U2.29
MIDI_THRU: J2.4, R3.2, U2.41
unnamed: C1.1, J5.1
unnamed: D2.2, R5.1
unnamed: D3.2, R6.1
unnamed: D4.2, R7.1
unnamed: D5.2, R8.1
unnamed: J1.4, R1.1
unnamed: J3.4, R4.1
unnamed: J4.4, R3.1
SPDIF_OUT: C1.2, J2.5, U2.44

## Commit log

2021-04-30 add gerber zip.
2021-05-08 Update issue templates
2021-05-14 Initial version of the extended board. Untested.
2021-05-14 fix for 3d view.
2021-05-14 Teaser for the extended board.
2021-06-11 removed unnecessary file.
2021-06-17 updated schematic
2021-06-21 nicer schematic, control voltage, power supply, power cleanups
2021-06-21 initial extended pcb 1.1 placement
2021-06-21 fixes
2021-06-26 power updates.
2021-06-26 first routes.
2021-06-27 fitted the 6.35mm audio jack which was too small. Added gerbers. ERC seems fine.
2021-07-12 initial commit for UI code
2021-07-13 building structure
2021-07-14 more structure
2021-07-18 more cleanups, more structure
2021-07-18 fix for memory leaks
2021-07-19 serial remote control via processing
2021-07-27 simulator ui done
2021-08-01 documentation for the display connection.
2021-08-01 development pcb to connect the display to avoid unnecessary cabling.
2021-08-01 prototype for mcp23017 multiplexed buttons
2021-08-02 removed softwareserial, moved hacky stuff to ctrlboard class. switching voices up and down kinda works, but is still very hacky.
2021-08-02 some cleanups
2021-08-06 xfm2 serial communication class
2021-08-06 cleanups
2021-08-07 fixes for the serial code
2021-08-07 cleanups, pitch eg implementation
2021-08-15 clion platformio support. clang-tidy cleanups. todo comments (serial blocking is bad when tx is not connected).
2021-08-15 consistent formatting.
2021-09-12 xva1 patch names are shown on the display.
2021-09-12 updates for the extended xfm2 board: replacement of opamp components, logic level converter 5v<->3.3v and pull ups for uart.
2021-09-19 xfm2/xva pcb version 1.3 (untested, don't use yet).
2021-09-20 v1.31 pcb. fix for a weird oval hole in the used usb-c connector footprint.
2021-10-02 Next bugfix version 1.33.
2021-10-02 missed a file...
2021-10-23 bugfix incl. gerber v1.34 for the extended board.
2021-10-23 fix schema date for v1.34
2021-10-24 unwired ui develeopment board is mostly done.
2021-10-25 lots of ui board routing
2021-10-28 fully routed.
2021-10-28 small corrections + mounting holes.
2021-10-29 small changes + gerber for front panel dev board
2021-10-29 updated footprint for the crystal
2022-03-06 version 1.40 with kicad 6 migration
2022-03-06 v1.40 including jlcpcb assembly files.
2022-03-06 corrections.
2022-03-06 updated gerber
2022-03-07 removed mcp6004 from assembly file (so-14 footprint slightly too big).
2022-03-07 cypress configuration
2022-03-09 example buttons for each multiplexer.
2022-03-29 assembly files corrections.
2022-04-17 pdf schematic + layout.
